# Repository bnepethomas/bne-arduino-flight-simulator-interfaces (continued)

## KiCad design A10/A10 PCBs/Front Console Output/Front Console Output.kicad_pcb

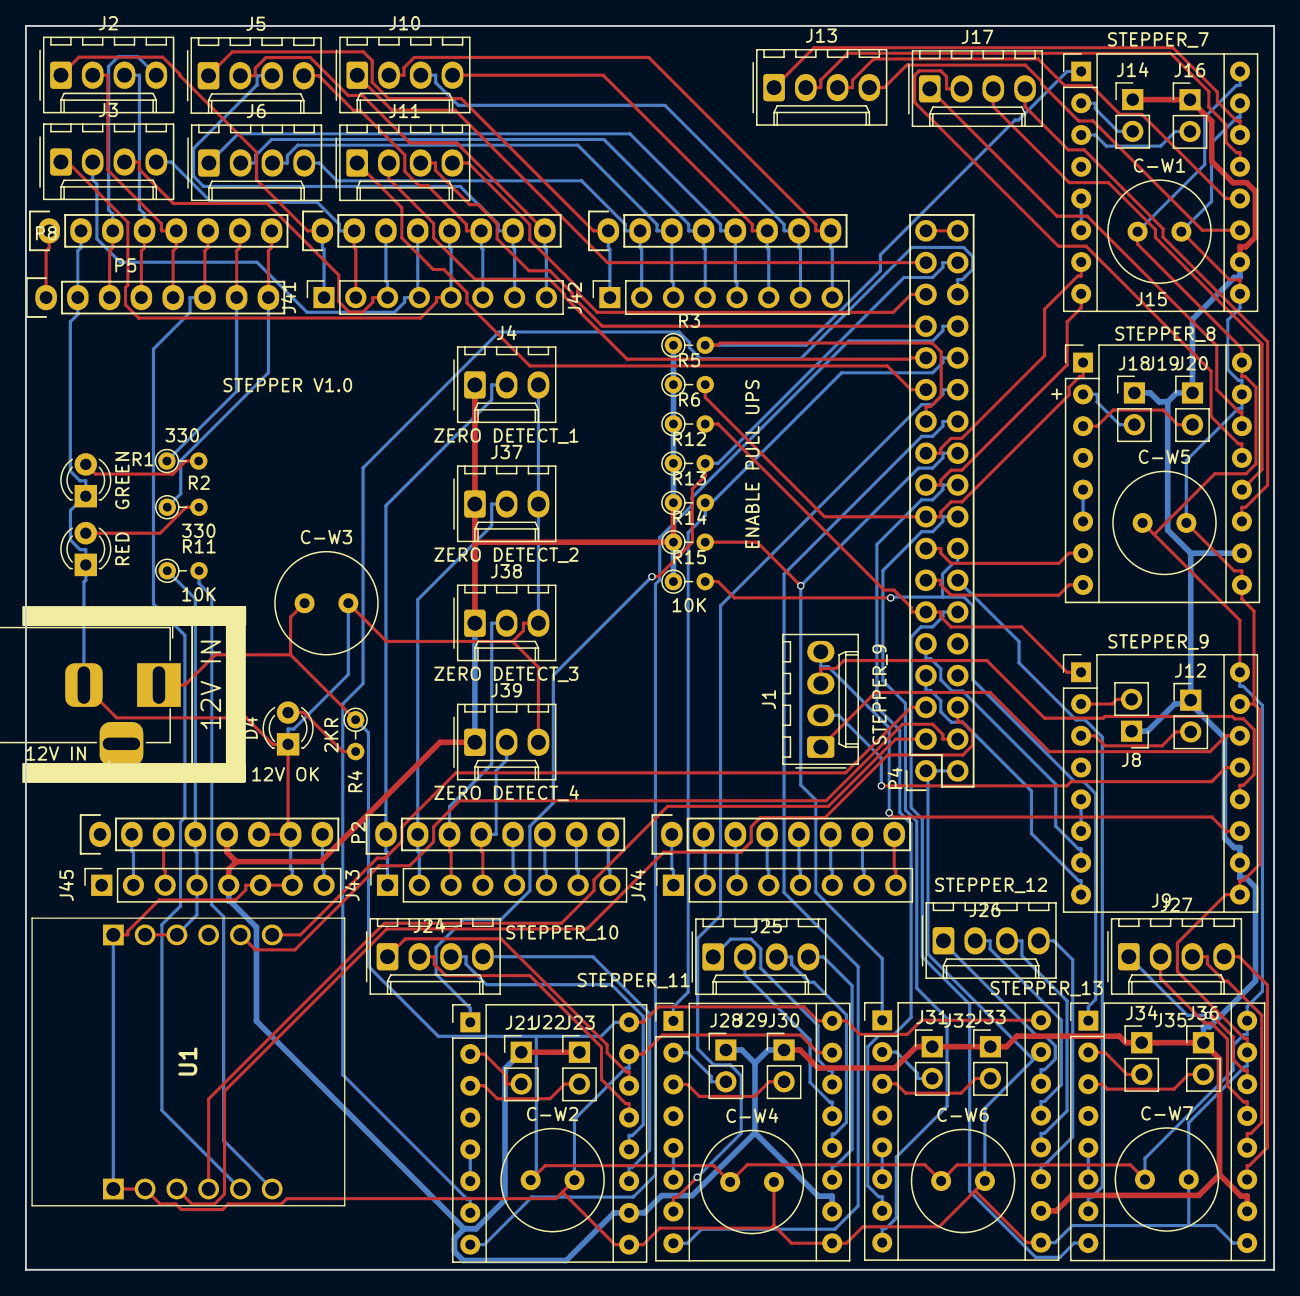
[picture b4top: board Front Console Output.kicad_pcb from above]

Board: 2 copper layers, 99.8 x 99.5 mm, 74 parts (0 on the bottom side), 130 nets.

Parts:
C-W1, C-W2, C-W3, C-W4, C-W5, C-W6, C-W7: 100uF; C_Radial_D8.0mm_H7.0mm_P3.50mm
D1: GREEN; LED_D3.0mm
D2: RED; LED_D3.0mm
D4: LED; LED_D3.0mm
J1: STEPPER_9; Molex_KK-254_AE-6410-04A_1x04_P2.54mm_Vertical
J2: STEPPER_1; Molex_KK-254_AE-6410-04A_1x04_P2.54mm_Vertical
J3: STEPPER_2; Molex_KK-254_AE-6410-04A_1x04_P2.54mm_Vertical
J4: ZERO DETECT_1; Molex_KK-254_AE-6410-03A_1x03_P2.54mm_Vertical
J5: STEPPER_3; Molex_KK-254_AE-6410-04A_1x04_P2.54mm_Vertical
J6: STEPPER_4; Molex_KK-254_AE-6410-04A_1x04_P2.54mm_Vertical
J7: STEPPER IN 12-20VDC; BarrelJack_Horizontal
J8: 9_MS1; PinHeader_1x02_P2.54mm_Vertical
J9: STEPPER_9; Pololu_Breakout-16_15.2x20.3mm
J10: STEPPER_5; Molex_KK-254_AE-6410-04A_1x04_P2.54mm_Vertical
J11: STEPPER_6; Molex_KK-254_AE-6410-04A_1x04_P2.54mm_Vertical
J12: 9_MS2; PinHeader_1x02_P2.54mm_Vertical
J13: STEPPER_7; Molex_KK-254_AE-6410-04A_1x04_P2.54mm_Vertical
J14: 7_MS1; PinHeader_1x02_P2.54mm_Vertical
J15: STEPPER_7; Pololu_Breakout-16_15.2x20.3mm
J16: 7_MS2; PinHeader_1x02_P2.54mm_Vertical
J17: STEPPER_8; Molex_KK-254_AE-6410-04A_1x04_P2.54mm_Vertical
J18: 8_MS1; PinHeader_1x02_P2.54mm_Vertical
J19: STEPPER_8; Pololu_Breakout-16_15.2x20.3mm
J20: 8_MS2; PinHeader_1x02_P2.54mm_Vertical
J21: 10_MS1; PinHeader_1x02_P2.54mm_Vertical
J22: STEPPER_10; Pololu_Breakout-16_15.2x20.3mm
J23: 10_MS2; PinHeader_1x02_P2.54mm_Vertical
J24: STEPPER_10; Molex_KK-254_AE-6410-04A_1x04_P2.54mm_Vertical
J25: STEPPER_11; Molex_KK-254_AE-6410-04A_1x04_P2.54mm_Vertical
J26: STEPPER_12; Molex_KK-254_AE-6410-04A_1x04_P2.54mm_Vertical
J27: STEPPER_13; Molex_KK-254_AE-6410-04A_1x04_P2.54mm_Vertical
J28: 11_MS1; PinHeader_1x02_P2.54mm_Vertical
J29: STEPPER_11; Pololu_Breakout-16_15.2x20.3mm
J30: 11_MS2; PinHeader_1x02_P2.54mm_Vertical
J31: 12_MS1; PinHeader_1x02_P2.54mm_Vertical
J32: STEPPER_12; Pololu_Breakout-16_15.2x20.3mm
J33: 12_MS2; PinHeader_1x02_P2.54mm_Vertical
J34: 13_MS1; PinHeader_1x02_P2.54mm_Vertical
J35: STEPPER_13; Pololu_Breakout-16_15.2x20.3mm
J36: 13_MS2; PinHeader_1x02_P2.54mm_Vertical
J37: ZERO DETECT_2; Molex_KK-254_AE-6410-03A_1x03_P2.54mm_Vertical
J38: ZERO DETECT_3; Molex_KK-254_AE-6410-03A_1x03_P2.54mm_Vertical
J39: ZERO DETECT_4; Molex_KK-254_AE-6410-03A_1x03_P2.54mm_Vertical
J41: PWM; PinSocket_1x08_P2.54mm_Vertical
J42: Communication; PinSocket_1x08_P2.54mm_Vertical
J43, J44: Analog; PinSocket_1x08_P2.54mm_Vertical
J45: Power; PinSocket_1x08_P2.54mm_Vertical
P1: Power; Socket_Strip_Arduino_1x08
P2, P3: Analog; Socket_Strip_Arduino_1x08
P4: Digital; Socket_Strip_Arduino_2x18
P5, P6, P8: PWM; Socket_Strip_Arduino_1x08
P7: Communication; Socket_Strip_Arduino_1x08
R1: 330; R_Axial_DIN0204_L3.6mm_D1.6mm_P2.54mm_Vertical
R2: 330; PT_R_Axial_DIN0204_L3.6mm_D1.6mm_P2.54mm_Vertical
R3, R5, R6, R12, R13, R14, R15: 10K; R_Axial_DIN0204_L3.6mm_D1.6mm_P2.54mm_Vertical
R4: 2000; R_Axial_DIN0204_L3.6mm_D1.6mm_P2.54mm_Vertical
R11: 10K; PT_R_Axial_DIN0204_L3.6mm_D1.6mm_P2.54mm_Vertical
U1: USR-ES1; USRES1

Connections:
+3V3: J45.4, P1.4, R11.1, U1.B2 (3V3_1), U1.B3 (3V3_2)
+5VL: J4.1, J8.1, J9.10, J12.1, J14.1, J15.10, J16.1, J18.1, J19.10, J20.1, J21.1, J22.10, J23.1, J28.1, J29.10, J30.1, J31.1, J32.10, J33.1, J34.1, J35.10, J36.1, J37.1, J38.1, J39.1, J45.5, P1.5, R3.1, R5.1, R6.1, R12.1, R13.1, R14.1, R15.1
/7_DIR: J15.8, P4.19
/7_EN: J15.1, P4.23, R3.2
/7_MS1: J14.2, J15.2
/7_MS2: J15.3, J16.2
/7_STEP: J15.7, P4.21
/8_DIR: J19.8, P4.13
/8_EN: J19.1, P4.17, R5.2
/8_MS1: J18.2, J19.2
/8_MS2: J19.3, J20.2
/8_STEP: J19.7, P4.15
/9_DIR: J9.8, P4.7
/9_EN: J9.1, P4.11, R6.2
/9_MS1: J8.2, J9.2
/9_MS2: J9.3, J12.2
/9_STEP: J9.7, P4.9
/10_DIR: J22.8, P4.30
/10_EN: J22.1, P4.34, R12.2
/10_MS1: J21.2, J22.2
/10_MS2: J22.3, J23.2
/10_STEP: J22.7, P4.32
/11_DIR: J29.8, P4.24
/11_EN: J29.1, P4.28, R13.2
/11_MS1: J28.2, J29.2
/11_MS2: J29.3, J30.2
/11_STEP: J29.7, P4.26
/12_DIR: J32.8, P4.18
/12_EN: J32.1, P4.22, R14.2
/12_MS1: J31.2, J32.2
/12_MS2: J32.3, J33.2
/12_STEP: J32.7, P4.20
/13_DIR: J35.8, P4.12
/13_EN: J35.1, P4.16, R15.2
/13_MS1: J34.2, J35.2
/13_MS2: J35.3, J36.2
/13_STEP: J35.7, P4.14
/*2: J5.4, J41.6, P6.6
/*3: J3.1, J41.5, P6.5
/*4: J3.2, J41.4, P6.4
/*5: J3.3, J41.3, P6.3
/*6: J3.4, J41.2, P6.2
/*7: J2.1, J41.1, P6.1
/*8: P5.8, P8.8, R2.1
/*9: P5.7, P8.7, R1.1
/*11: J2.2, P5.5, P8.5
/*12: J2.3, P5.4, P8.4
/*13: J2.4, P5.3, P8.3
/A0: J4.2, J43.1, P2.1
/A1: J37.2, J43.2, P2.2
/A2: J38.2, J43.3, P2.3
/A3: J39.2, J43.4, P2.4
/A4: J43.5, P2.5
/A5: J43.6, P2.6
/A6: J43.7, P2.7
/A7: J43.8, P2.8
/A8: J44.1, P3.1
/A9: J44.2, P3.2
/A10: J44.3, P3.3
/A11: J44.4, P3.4
/A12: J44.5, P3.5
/A13: J44.6, P3.6
/A14: J44.7, P3.7
/A15: J44.8, P3.8
/AREF: P5.1, P8.1
/IOREF: J45.2, P1.2
/ROLL_STEP_V+: C-W1.1, C-W2.1, C-W3.1, C-W4.1, C-W5.1, C-W6.1, C-W7.1, J7.1, J9.16, J15.16, J19.16, J22.16, J29.16, J32.16, J35.16, R4.1
/RX0/0: J5.2, J41.8, P6.8
/RX1/19: J10.4, J42.6, P7.6
/RX2/17: J6.2, J42.4, P7.4
/RX3/15: J6.4, J42.2, P7.2
/Reset: J45.3, P1.3
/SCL/21: J10.2, J42.8, P7.8
/SDA/20: J10.3, J42.7, P7.7
/STEPPER_3_B: J5.3, J41.7, P6.7
/STEPPER_3_D: J5.1, J42.1, P7.1
/STEPPER_4_B: J6.3, J42.3, P7.3
/STEPPER_4_D: J6.1, J42.5, P7.5
/STEPPER_5_D: J10.1, P4.33
/STEPPER_6_A: J11.4, P4.31
/STEPPER_6_B: J11.3, P4.29
/STEPPER_6_C: J11.2, P4.27
/STEPPER_6_D: J11.1, P4.25
/STEPPER_7_A: J13.4, J15.11
/STEPPER_7_B: J13.3, J15.12
/STEPPER_7_C: J13.2, J15.13
/STEPPER_7_D: J13.1, J15.14
/STEPPER_8_A: J17.4, J19.11
/STEPPER_8_B: J17.3, J19.12
/STEPPER_8_C: J17.2, J19.13
/STEPPER_8_D: J17.1, J19.14
/STEPPER_9_A: J1.4, J9.11
/STEPPER_9_B: J1.3, J9.12
/STEPPER_9_C: J1.2, J9.13
/STEPPER_9_D: J1.1, J9.14
/STEPPER_10_A: J22.11, J24.4
/STEPPER_10_B: J22.12, J24.3
/STEPPER_10_C: J22.13, J24.2
/STEPPER_10_D: J22.14, J24.1
/STEPPER_11_A: J25.4, J29.11
/STEPPER_11_B: J25.3, J29.12
/STEPPER_11_C: J25.2, J29.13
/STEPPER_11_D: J25.1, J29.14
/STEPPER_12_A: J26.4, J32.11
/STEPPER_12_B: J26.3, J32.12
/STEPPER_12_C: J26.2, J32.13
/STEPPER_12_D: J26.1, J32.14
/STEPPER_13_A: J27.4, J35.11
/STEPPER_13_B: J27.3, J35.12
/STEPPER_13_C: J27.2, J35.13
/STEPPER_13_D: J27.1, J35.14
ES1_RST: P4.4, U1.B5 (RST)
GND: C-W1.2, C-W2.2, C-W3.2, C-W4.2, C-W5.2, C-W6.2, C-W7.2, D1.1 (K), D2.1 (K), D4.1 (K), J4.3, J7.2, J9.9, J9.15, J15.9, J15.15, J19.9, J19.15, J22.9, J22.15, J29.9, J29.15, J32.9, J32.15, J35.9, J35.15, J37.3, J38.3, J39.3, J45.6, J45.7, P1.6, P1.7, P4.1, P4.2, P5.2, P8.2, U1.A1 (GND_1), U1.A2 (GND_2), U1.B1 (GND_3)
MISO: P4.5, U1.B6 (MISO)
MOSI: P4.6, U1.A3 (MOSI)
unnamed: D1.2 (A), R1.2
unnamed: D2.2 (A), R2.2
unnamed: D4.2 (A), R4.2
unnamed: J9.5, J9.6
unnamed: J15.5, J15.6
unnamed: J19.5, J19.6
unnamed: J22.5, J22.6
unnamed: J29.5, J29.6
unnamed: J32.5, J32.6
unnamed: J35.5, J35.6
unnamed: P4.35, P4.36
unnamed: R11.2, U1.A6 (INT)
SCLK: P4.3, U1.A4 (SCLK)
SS: P5.6, P8.6, U1.A5 (CS)
VCC: J45.8, P1.8

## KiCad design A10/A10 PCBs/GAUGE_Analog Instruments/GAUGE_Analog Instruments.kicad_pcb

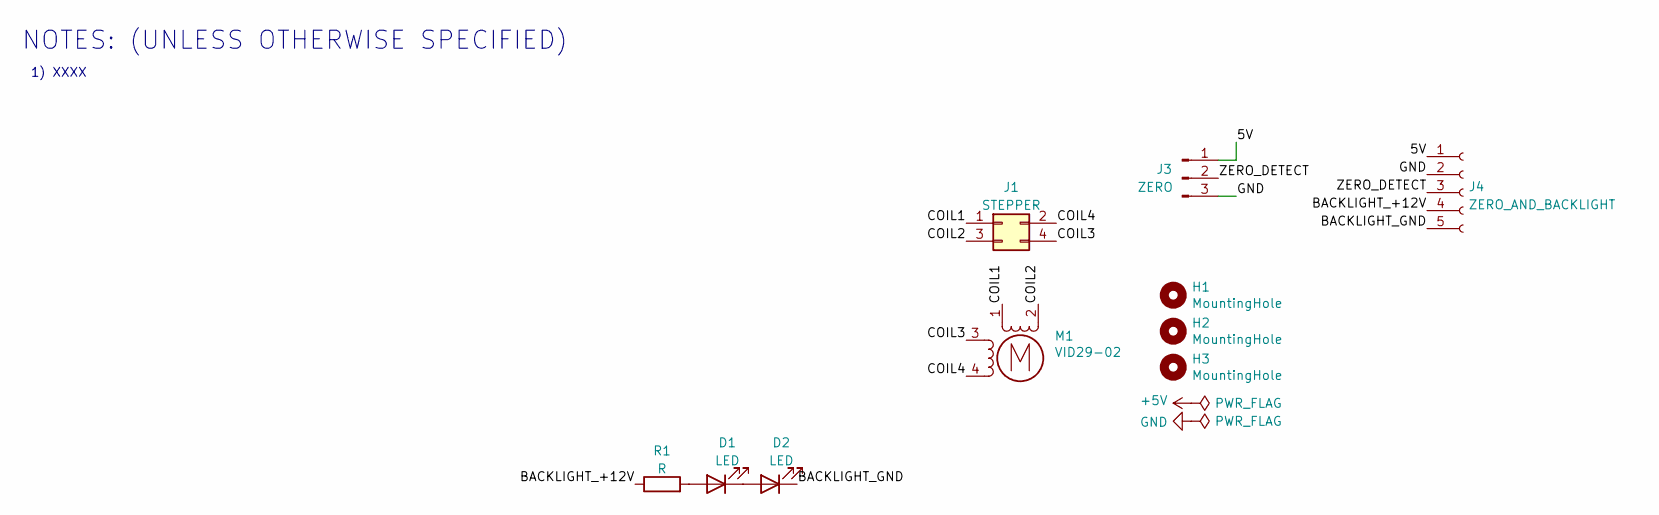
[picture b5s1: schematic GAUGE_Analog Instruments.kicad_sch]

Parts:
D1, D2: LED; LED_D5.0mm
H1, H2, H3: MountingHole; MountingHole_2.5mm
J1: STEPPER; Molex_PicoBlade_53047-0410_1x04_P1.25mm_Vertical
J3: ZERO; PinHeader_1x03_P2.54mm_Vertical
J4: ZERO_AND_BACKLIGHT; Molex_PicoBlade_53047-0510_1x05_P1.25mm_Vertical
M1: VID29-02
R1: R; R_Axial_DIN0204_L3.6mm_D1.6mm_P1.90mm_Vertical

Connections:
/5V: J3.1, J4.1
/BACKLIGHT_+12V: J4.4, R1.1
/BACKLIGHT_GND: D2.1 (K), J4.5
/COIL1: J1.1, M1.1
/COIL2: J1.3, M1.2 (-)
/COIL3: J1.4, M1.3
/COIL4: J1.2, M1.4
/ZERO_DETECT: J3.2, J4.3
GND: J3.3, J4.2
unnamed: D1.1 (K), D2.2 (A)
unnamed: D1.2 (A), R1.2

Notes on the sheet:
1) XXXX
NOTES: (UNLESS OTHERWISE SPECIFIED)

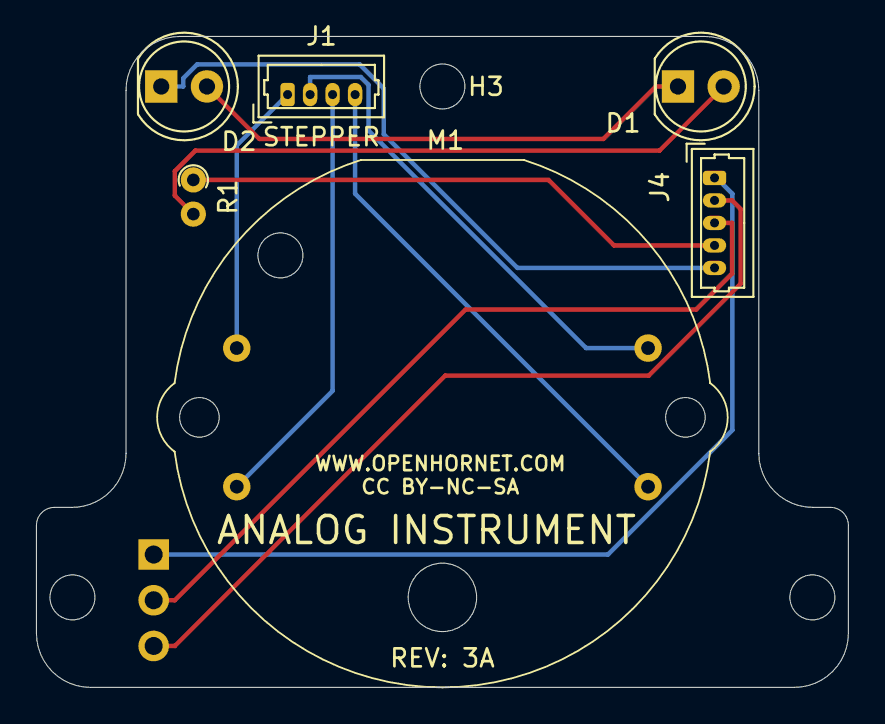
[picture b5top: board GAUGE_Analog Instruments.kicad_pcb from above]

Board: 2 copper layers, 45.1 x 36.2 mm, 10 parts (1 on the bottom side), 11 nets.

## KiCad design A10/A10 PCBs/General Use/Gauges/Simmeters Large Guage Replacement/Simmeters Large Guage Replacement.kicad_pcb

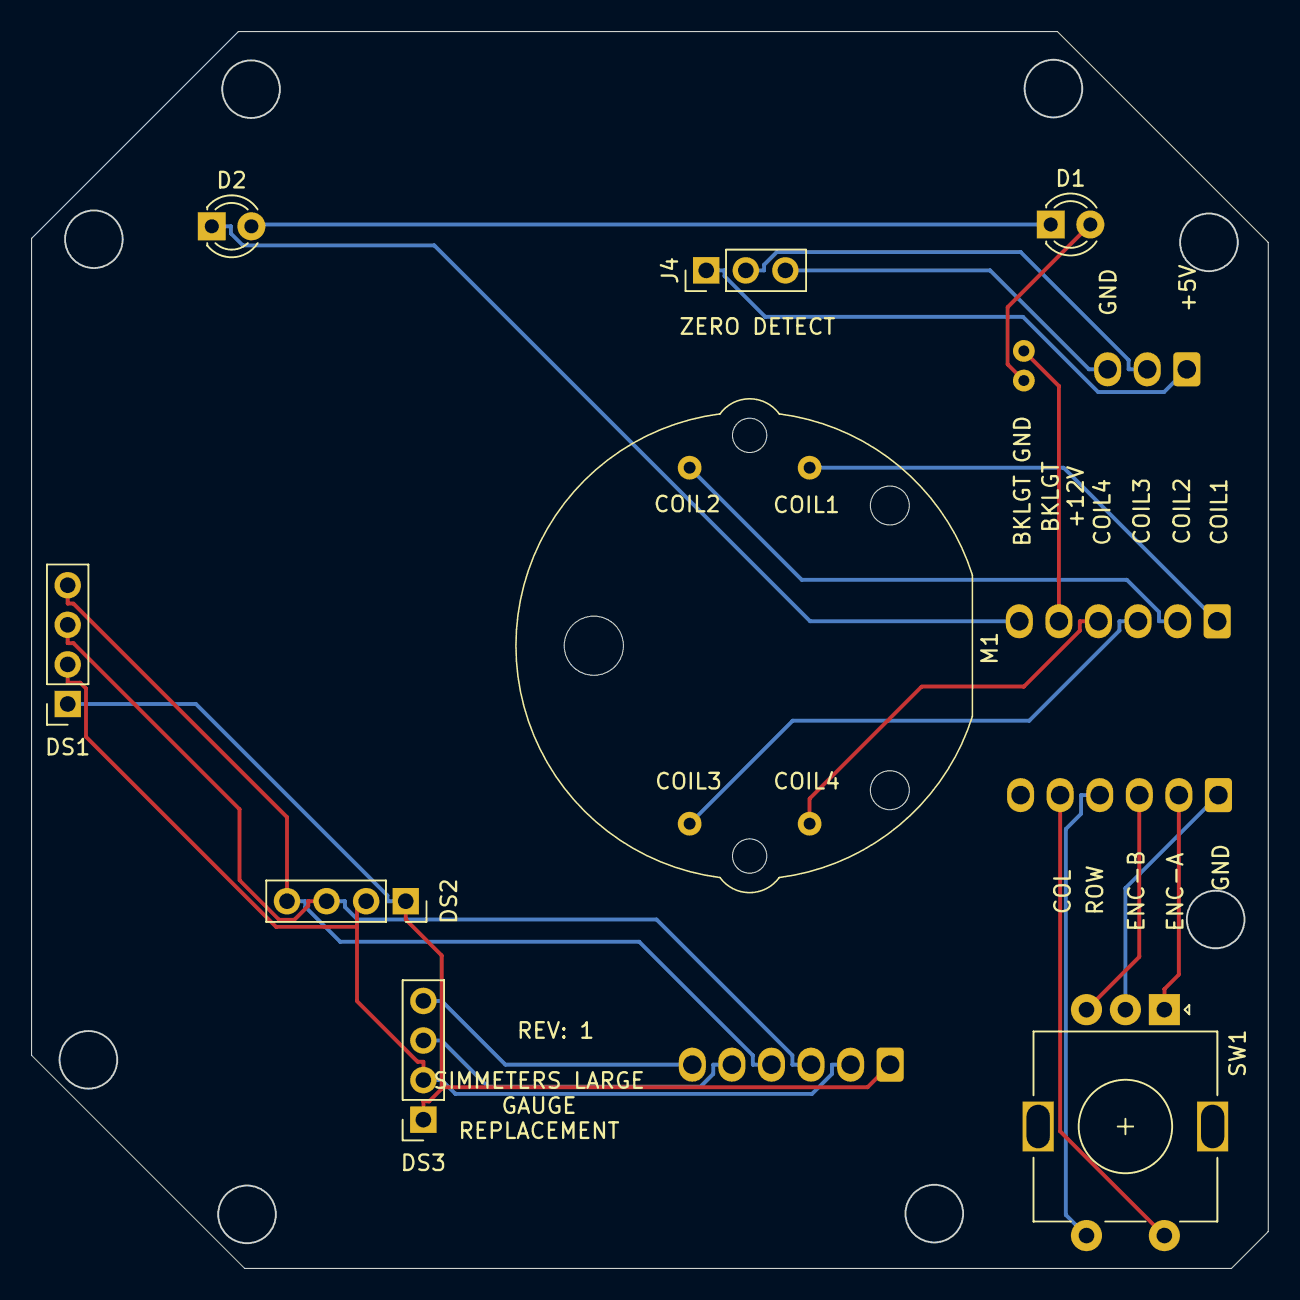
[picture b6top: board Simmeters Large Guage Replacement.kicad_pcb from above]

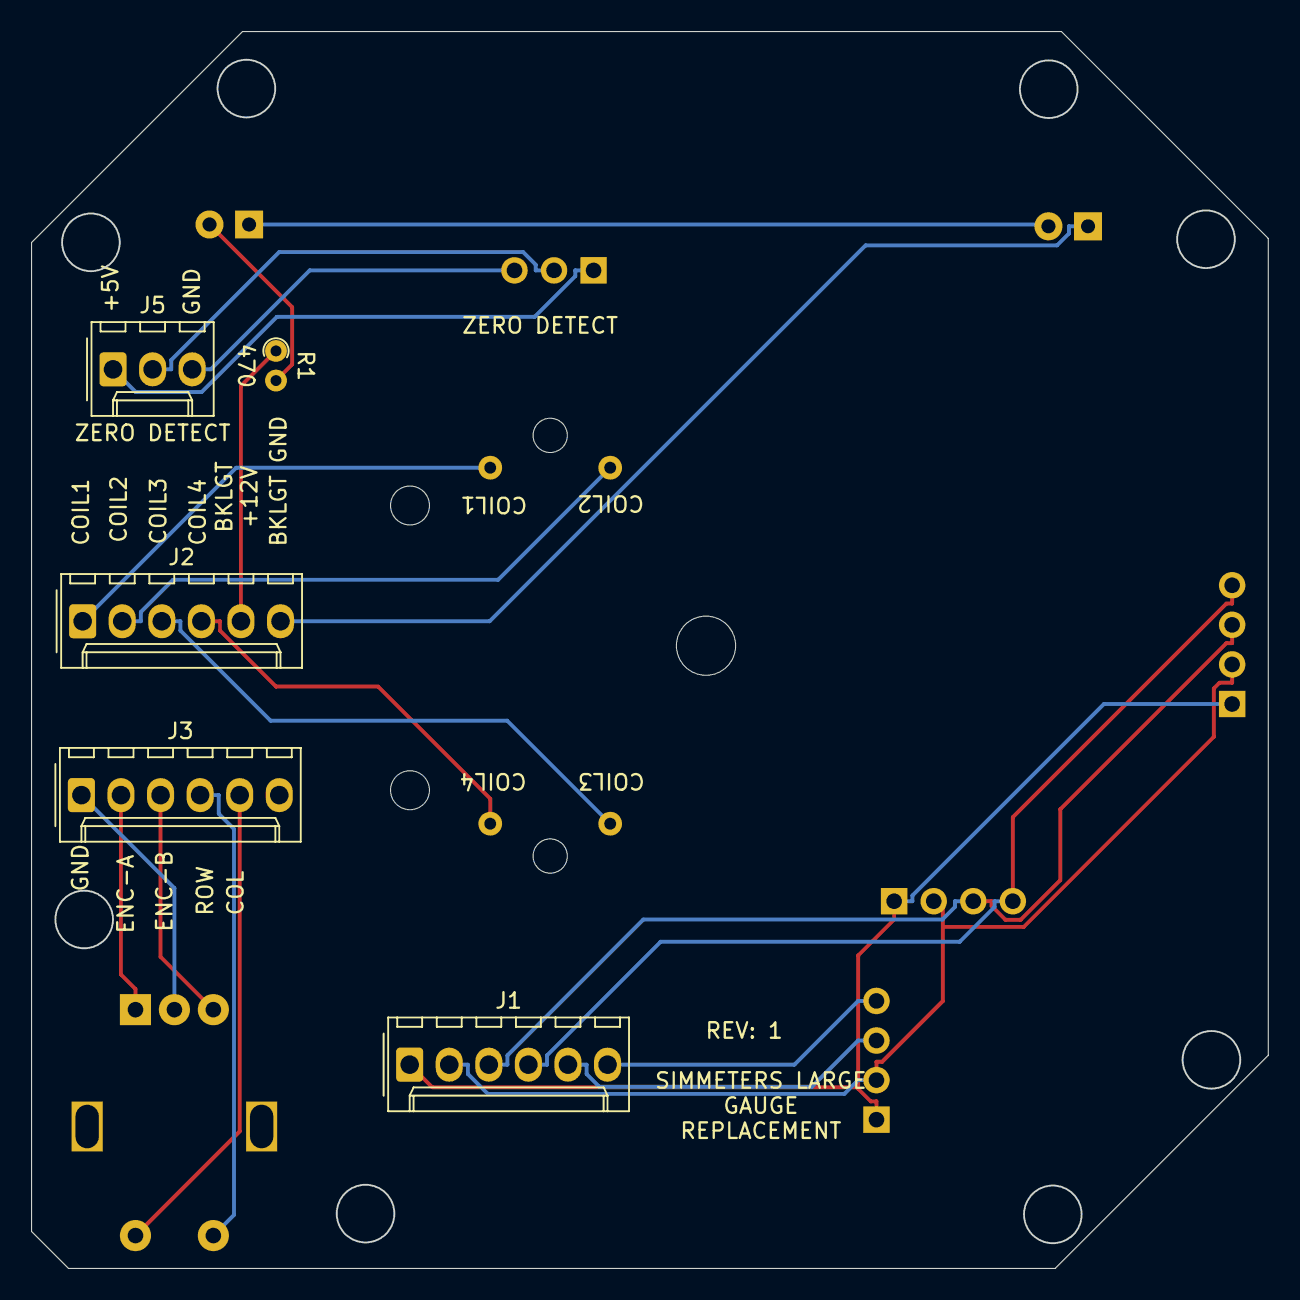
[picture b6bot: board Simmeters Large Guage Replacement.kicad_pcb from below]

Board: 2 copper layers, 79.4 x 79.4 mm, 13 parts (5 on the bottom side), 22 nets.

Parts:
D1, D2: LED; LED_D3.0mm
DS1, DS2: 10K_ALT_DISP; PinSocket_1x04_P2.54mm_Vertical
DS3: PRESS_DISP; PinSocket_1x04_P2.54mm_Vertical
J1: OLED; Molex_KK-254_AE-6410-06A_1x06_P2.54mm_Vertical
J2: STEPPER; Molex_KK-254_AE-6410-06A_1x06_P2.54mm_Vertical
J3: ENCODER; Molex_KK-254_AE-6410-06A_1x06_P2.54mm_Vertical
J4: ZERO; PinHeader_1x03_P2.54mm_Vertical
J5: ZERO DETECT; Molex_KK-254_AE-6410-03A_1x03_P2.54mm_Vertical
M1: VID29-02
R1: 470; R_Axial_DIN0204_L3.6mm_D1.6mm_P1.90mm_Vertical
SW1: RotaryEncoder_Switch; RotaryEncoder_Alps_EC11E-Switch_Vertical_H20mm

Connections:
+3V3: DS1.2, DS2.2, DS3.2, J1.2
+5V: J4.1, J5.1
/BACKLIGHT_+12V: J2.5, R1.1
/BACKLIGHT_GND: D2.1 (K), J2.6
/COIL1: J2.1, M1.1
/COIL2: J2.2, M1.2 (-)
/COIL3: J2.3, M1.3
/COIL4: J2.4, M1.4
/COL: J3.5, SW1.S2
/ENCODER B: J3.3, SW1.B
/ENCODER-A: J3.2, SW1.A
/ENCORDER GND: J3.1, SW1.C
/ROW: J3.4, SW1.S1
/SC0: DS1.3, DS2.3, J1.3
/SC1: DS3.3, J1.5
/SD0: DS1.4, DS2.4, J1.4
/SD1: DS3.4, J1.6
/ZERO_DETECT: J4.2, J5.2
GND: DS1.1, DS2.1, DS3.1, J1.1
GND1: J4.3, J5.3
unnamed: D1.2 (A), R1.2
unnamed: D1.1 (K), D2.2 (A)

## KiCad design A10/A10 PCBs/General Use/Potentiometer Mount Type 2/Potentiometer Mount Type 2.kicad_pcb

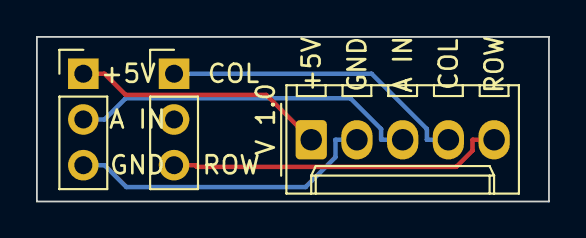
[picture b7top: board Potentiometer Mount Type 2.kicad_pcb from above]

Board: 2 copper layers, 28.4 x 9.1 mm, 3 parts (0 on the bottom side), 5 nets.

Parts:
J1: POT; Molex_KK-254_AE-6410-05A_1x05_P2.54mm_Vertical
RV1: R_Potentiometer_US; PinHeader_1x03_P2.54mm_Vertical
SW1: SW_SPDT; PinHeader_1x03_P2.54mm_Vertical

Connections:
/+5V: J1.1, RV1.1
/ANALOG_GND: J1.2, RV1.3
/ANALOG_IN: J1.3, RV1.2
/SWITCH_COL: J1.4, SW1.1 (A)
/SWITCH_ROW: J1.5, SW1.3 (C)
